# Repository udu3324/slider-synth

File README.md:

# Slider Synth

A synth that uses a linear touch sensor with a force sensor underneath to create cool sounds. It is inspired by the modulin by wintergatan. Powered by the esp32-s3 and mozzi library.

## Purpose

I built this pcb to make my diy setup more professional. I originally hooked everything up with an arduino but was really hard to cary around without dropping the breadboard or unplugging something. This design leaves it hot pluggable as well as super professional and more polished. 

## Schematic

## Additional Notes

[rotary encoder model](https://github.com/KiCad/kicad-packages3D/issues/547)

[sot-223 model](https://grabcad.com/library/discrete-smd-1/details?folder_id=1300113)

## BOM

I am supplying my own esp32-s3, rotary encoder, buttons, leds, and some other stuff that would cause the price to spike up to $30

I also have the linear softpot potentiometer, force sensitive resistor, and plywood strip on hand. **They total about $50** (plywood was scrap/free)

**Before fabricating the pcb, make sure the traces for the FSR is going to IO4 and not IO38!!!**

| Price  | Part Number            | Type     | LCSC Part   | Owner    | Designators          |   Qty | Manufacturer   |
|:-------|:-----------------------|:---------|:------------|:---------|:---------------------|------:|:---------------|
| $0.02  | CL21A106KAYNNNE        | Basic    | C15850      | System   | C4                   |     2 | JLCPCB         |
| $0.17  | CL21A476MQYNNNE        | Basic    | C16780      | System   | C3,C43,C45           |     6 | JLCPCB         |
| $0.03  | SS14                   | Basic    | C2480       | System   | D1                   |     2 | JLCPCB         |
| $0.02  | CL21B105KBFNNNE        | Basic    | C28323      | System   | C1                   |     2 | JLCPCB         |
| $2.11  | LM3940IMPX-3.3/NOPB    | Extended | C544820     | System   | U2                   |     2 | JLCPCB         |
| $0.05  | CC0805KRX7R9BB104      | Basic    | C49678      | System   | C48,C49,C5,C50,C6,C7 |    12 | JLCPCB         |
| $0.37  | LM386                  | Extended | C5157706    | System   | U33,U34              |     4 | JLCPCB         |
| $0.03  | CL21B474KBFNNNE        | Basic    | C13967      | System   | C2                   |     2 | JLCPCB         |
| $0.01  | 0805W8F0000T5E         | Basic    | C17477      | System   | R4,R5,R6             |     6 | JLCPCB         |
| $5.35  | MCP4922-E/SL           | Extended | C39851      | System   | U32                  |     2 | JLCPCB         |
| $0.01  | 0805W8F1002T5E         | Basic    | C17414      | System   | R13,R3               |     4 | JLCPCB         |
| $0.01  | 0805W8F100JT5E         | Basic    | C17415      | System   | R28,R29              |     4 | JLCPCB         |
| $2.24  | USB4105-GF-A-120       | Extended | C5184243    | System   | J1                   |     2 | JLCPCB         |
| $0.03  | 0805B333K500NT         | Basic    | C1739       | System   | C42,C44              |     4 | JLCPCB         |
| $0.01  | 0805W8F3300T5E         | Basic    | C17630      | System   | R10,R11,R8,R9        |     8 | JLCPCB         |
| $0.05  | CL21B473KBCNNNC        | Basic    | C53134      | Customer | C46,C47              |     4 | JLCPCB         |
| $0.01  | 0805W8F5101T5E         | Basic    | C27834      | System   | R1,R2                |     4 | JLCPCB         |
| $23.28 | **Total Part Price**   |          |             |          |                      |       |                |
|        |                        |          |             |          |                      |       |                |
| $37.24 | Merchandise Total      |          |             |          |                      |       |                |
| $26.56 | Shipping Estimate      |          |             |          |                      |       |                |
| $5.27  | Sales Tax              |          |             |          |                      |       |                |
| $20.49 | Customs duties & taxes |          |             |          |                      |       |                |
| $89.56 | **Grand Total**        |          |             |          |                      |       |                |

Actual total would be around ~$150 USD including my own components sourced.

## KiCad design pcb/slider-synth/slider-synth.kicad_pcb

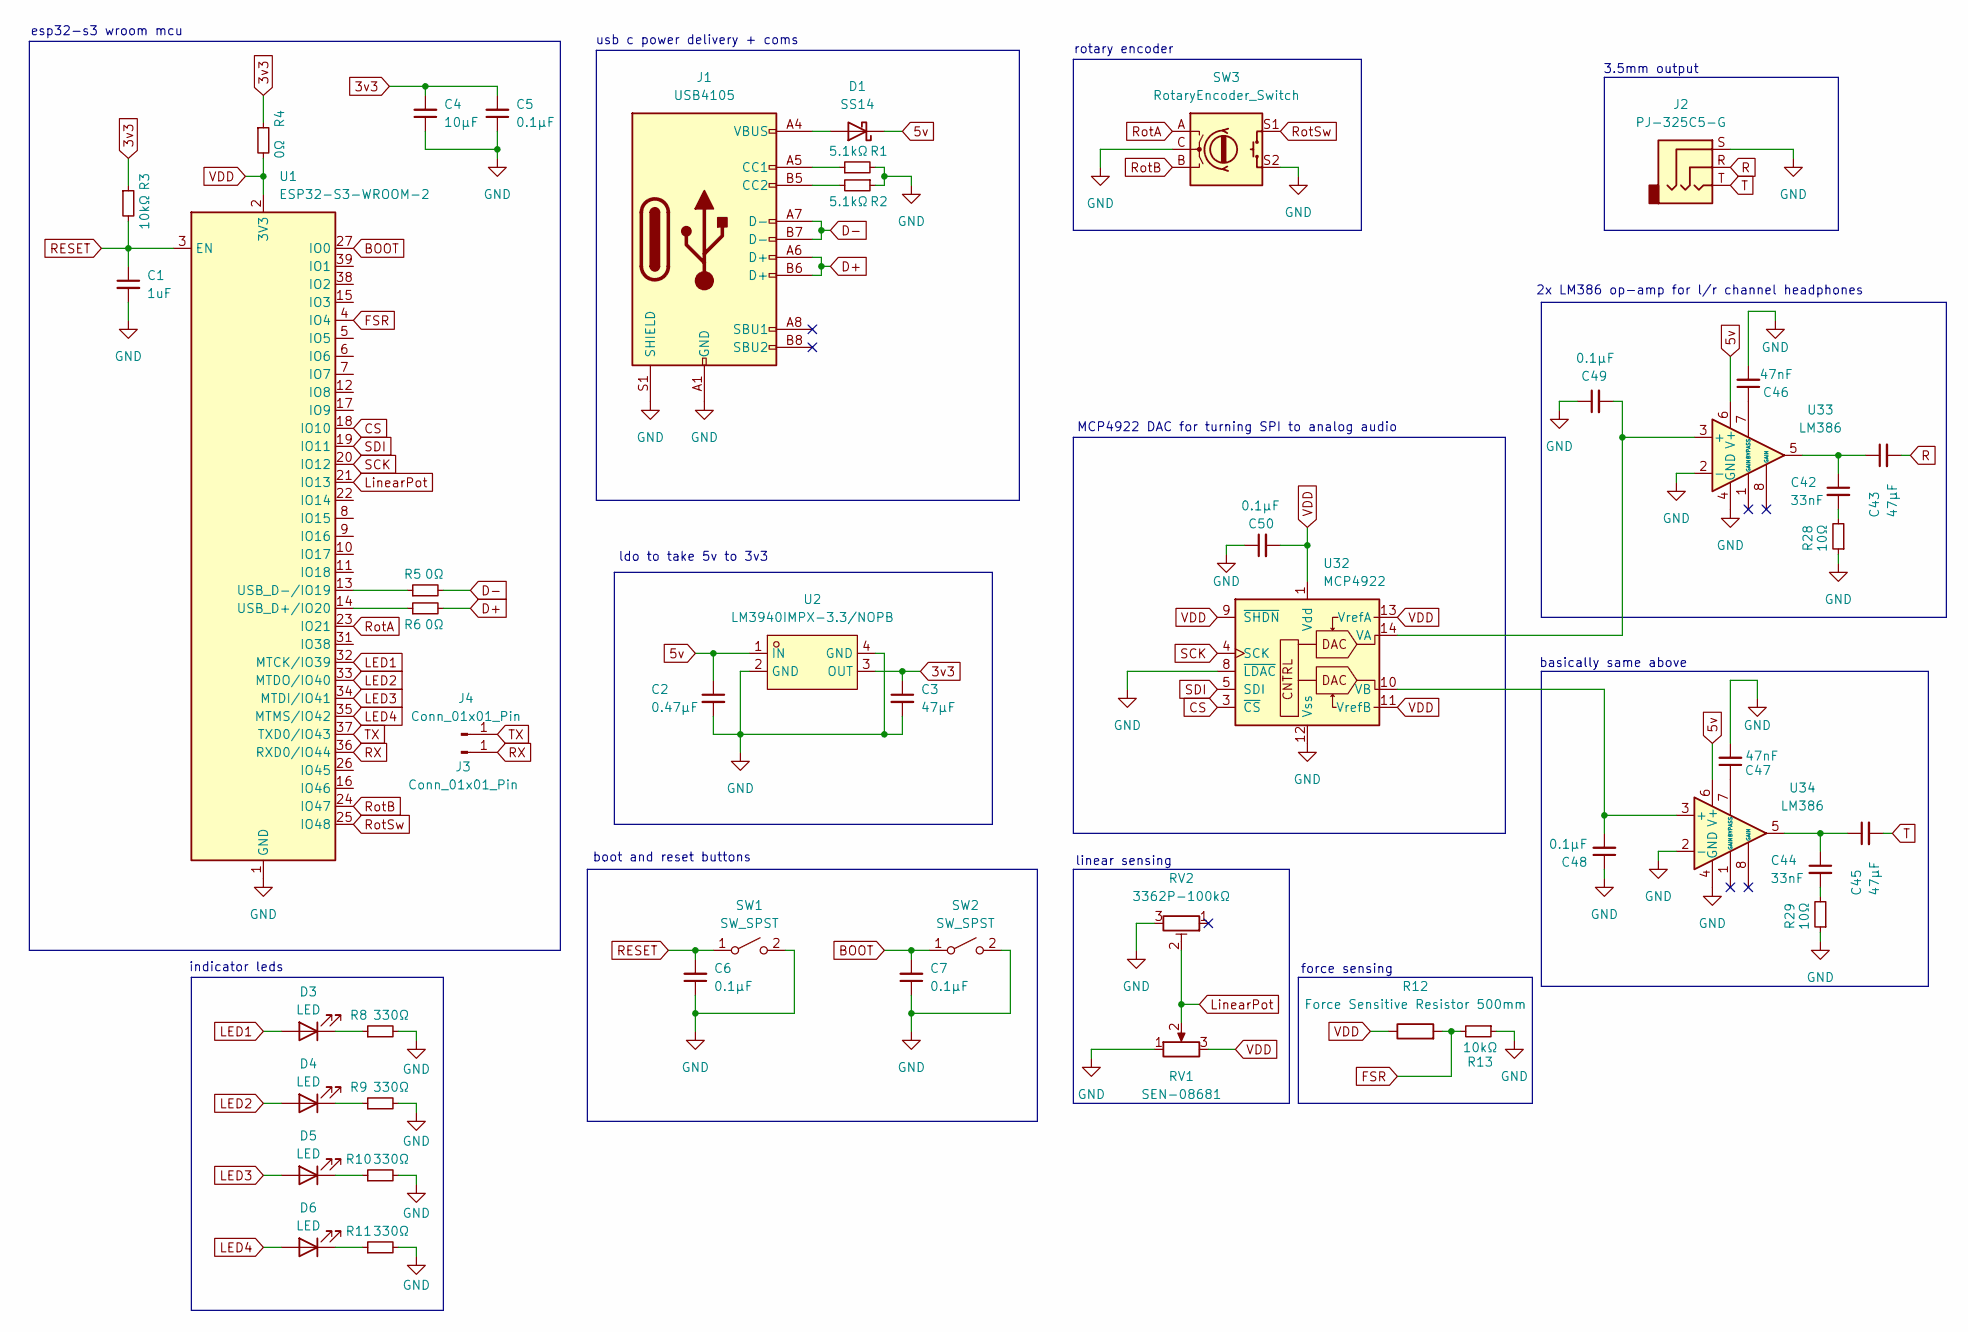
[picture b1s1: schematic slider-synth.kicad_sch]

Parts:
C1: 1uF; C_0805_2012Metric
C2: 0.47μF; C_0805_2012Metric
C3, C43, C45: 47μF; C_0805_2012Metric
C4: 10μF; C_0805_2012Metric
C5, C6, C7, C48, C49, C50: 0.1μF; C_0805_2012Metric
C42, C44: 33nF; C_0805_2012Metric
C46, C47: 47nF; C_0805_2012Metric
D1: SS14; D_SMA
D3, D4, D5, D6: LED; LED_D5.0mm
J1: USB4105; USB_C_Receptacle_GCT_USB4105-xx-A_16P_TopMnt_Horizontal
J2: PJ-325C5-G; Jack_3.5mm_CUI_SJ1-3535NG_Horizontal; LCSC C692438
J3, J4: Conn_01x01_Pin; PinHeader_1x01_P2.54mm_Vertical
R1, R2: 5.1kΩ; R_0805_2012Metric
R3, R13: 10kΩ; R_0805_2012Metric
R4, R5, R6: 0Ω; R_0805_2012Metric
R8, R9, R10, R11: 330Ω; R_0805_2012Metric
R12: Force Sensitive Resistor 500mm; PinSocket_1x02_P2.54mm_Vertical
R28, R29: 10Ω; R_0805_2012Metric
RV1: SEN-08681; PinSocket_1x03_P2.54mm_Vertical
RV2: 3362P-100kΩ; POT_3362P
SW1, SW2: SW_SPST; SW_PUSH_6mm
SW3: RotaryEncoder_Switch; RotaryEncoder_Alps_EC11E-Switch_Vertical_H20mm
U1: ESP32-S3-WROOM-2
U2: LM3940IMPX-3.3/NOPB; SOT-223-4_L6.5-W3.5-P2.30-LS7.0-BR; LCSC Part C544820
U32: MCP4922; SOIC-14_3.9x8.7mm_P1.27mm
U33, U34: LM386; SOIC-8_3.9x4.9mm_P1.27mm

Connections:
3v3: C3.1, C4.2, C5.2, R3.1, R4.1, U2.3 (OUT)
5v: C2.1, D1.1 (K), U2.1 (IN), U33.6 (V+), U34.6 (V+)
BOOT: C7.2, SW2.1 (A), U1.27 (IO0)
CS: U1.18 (IO10), U32.3 (~CS)
D+: J1.A6 (D+), J1.B6 (D+), R6.2
D-: J1.A7 (D-), J1.B7 (D-), R5.2
FSR: R12.2, R13.2, U1.4 (IO4)
GND: C1.2, C2.2, C3.2, C4.1, C5.1, C6.1, C7.1, C46.2, C47.2, C48.1, C49.1, C50.1, J1.A1 (GND), J1.A12 (GND), J1.B1 (GND), J1.B12 (GND), J1.S1 (SHIELD), J2.S, R1.2, R2.1, R8.2, R9.2, R10.2, R11.2, R13.1, R28.1, R29.1, RV1.1, RV2.3, SW1.2 (B), SW2.2 (B), SW3.C, SW3.S2, U1.1 (GND), U1.40 (GND), U1.41 (GND), U2.2 (GND), U2.4 (GND), U32.8 (~LDAC), U32.12 (Vss), U33.2 (-), U33.4 (GND), U34.2 (-), U34.4 (GND)
LED1: D3.2 (A), U1.32 (MTCK/IO39)
LED2: D4.2 (A), U1.33 (MTDO/IO40)
LED3: D5.2 (A), U1.34 (MTDI/IO41)
LED4: D6.2 (A), U1.35 (MTMS/IO42)
LinearPot: RV1.2, RV2.2, U1.21 (IO13)
unnamed: C42.1, C43.1, U33.5
unnamed: C42.2, R28.2
unnamed: C44.1, C45.1, U34.5
unnamed: C44.2, R29.2
unnamed: D1.2 (A), J1.A4 (VBUS), J1.A9 (VBUS), J1.B4 (VBUS), J1.B9 (VBUS)
unnamed: D3.1 (K), R8.1
unnamed: D4.1 (K), R9.1
unnamed: D5.1 (K), R10.1
unnamed: D6.1 (K), R11.1
unnamed: J1.A5 (CC1), R1.1
unnamed: J1.B5 (CC2), R2.2
unnamed: R6.1, U1.14 (USB_D+/IO20)
unnamed: R5.1, U1.13 (USB_D-/IO19)
unnamed: C49.2, U32.14 (VA), U33.3 (+)
unnamed: C48.2, U32.10 (VB), U34.3 (+)
unnamed: C46.1, U33.7 (BYPASS)
unnamed: C47.1, U34.7 (BYPASS)
R: C43.2, J2.R
RESET: C1.1, C6.2, R3.2, SW1.1 (A), U1.3 (EN)
RX: J3.1, U1.36 (RXD0/IO44)
RotA: SW3.A, U1.23 (IO21)
RotB: SW3.B, U1.24 (IO47)
RotSw: SW3.S1, U1.25 (IO48)
SCK: U1.20 (IO12), U32.4 (SCK)
SDI: U1.19 (IO11), U32.5 (SDI)
T: C45.2, J2.T
TX: J4.1, U1.37 (TXD0/IO43)
VDD: C50.2, R4.2, R12.1, RV1.3, U1.2 (3V3), U32.1 (Vdd), U32.9 (~SHDN), U32.11 (VrefB), U32.13 (VrefA)

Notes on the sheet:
esp32-s3 wroom mcu
MCP4922 DAC for turning SPI to analog audio
3.5mm output
force sensing
basically same above
rotary encoder
usb c power delivery + coms
ldo to take 5v to 3v3
2x LM386 op-amp for l/r channel headphones
boot and reset buttons
indicator leds
linear sensing

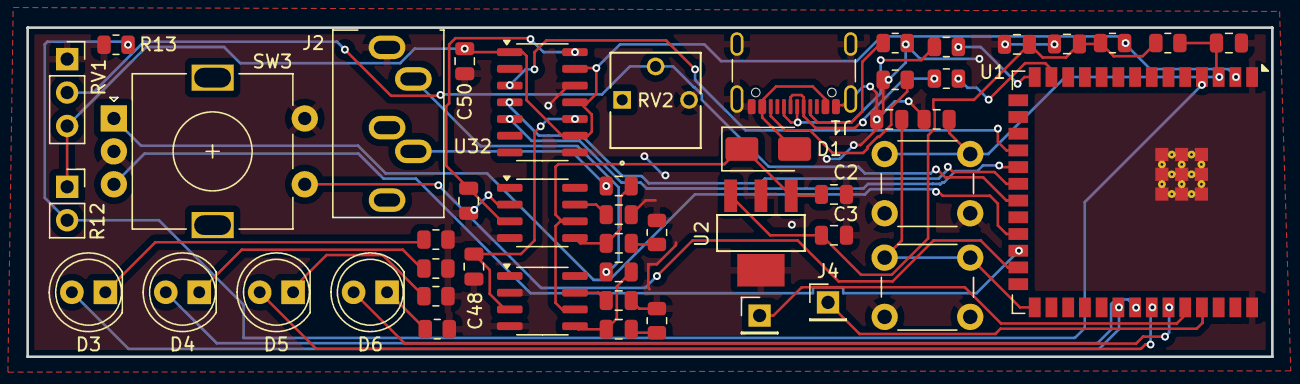
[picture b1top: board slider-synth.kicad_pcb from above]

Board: 2 copper layers, 94.6 x 25.0 mm, 49 parts (0 on the bottom side), 41 nets.

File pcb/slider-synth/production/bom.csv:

Designator,Footprint,Quantity,Value,LCSC Part #
C1,0805,1,1uF,
C2,0805,1,0.47μF,
"C3, C43, C45",0805,3,47μF,
C4,0805,1,10μF,
"C42, C44",0805,2,33nF,
"C46, C47",0805,2,0.05μF,
"C48, C49, C5, C50, C6, C7",0805,6,0.1μF,
D1,D_SMA,1,SS14,
"D3, D4, D5, D6",LED_D5.0mm,4,LED,
J1,USB_C_Receptacle_GCT_USB4105-xx-A_16P_TopMnt_Horizontal,1,USB4105,
J2,Jack_3.5mm_CUI_SJ1-3535NG_Horizontal,1,PJ-325C5-G,C692438
"J3, J4",PinHeader_1x01_P2.54mm_Vertical,2,Conn_01x01_Pin,
"R1, R2",0805,2,5.1kΩ,
"R10, R11, R8, R9",0805,4,330Ω,
R12,PinSocket_1x02_P2.54mm_Vertical,1,Force Sensitive Resistor 500mm,
"R13, R3",0805,2,10kΩ,
"R28, R29",0805,2,10Ω,
"R4, R5, R6",0805,3,0Ω,
RV1,PinSocket_1x03_P2.54mm_Vertical,1,SEN-08681,
RV2,POT_3362P,1,3362P-100kΩ,
"SW1, SW2",SW_PUSH_6mm,2,SW_SPST,
SW3,RotaryEncoder_Alps_EC11E-Switch_Vertical_H20mm,1,RotaryEncoder_Switch,
U1,ESP32-S3-WROOM-2,1,ESP32-S3-WROOM-2,
U2,SOT-223-4_L6.5-W3.5-P2.30-LS7.0-BR,1,LM3940IMPX-3.3/NOPB,C544820
U32,SOIC-14_3.9x8.7mm_P1.27mm,1,MCP4922,
"U33, U34",SOIC-8_3.9x4.9mm_P1.27mm,2,LM386,

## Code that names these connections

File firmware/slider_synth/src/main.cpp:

#include "MozziConfigValues.h"  // for named option values

#define MOZZI_AUDIO_MODE MOZZI_OUTPUT_EXTERNAL_TIMED
#define MOZZI_AUDIO_BITS 24
#define MOZZI_CONTROL_RATE 256 // Hz, powers of 2 are most reliable

#include <Mozzi.h>
#include <Oscil.h>
#include <tables/sin2048_int8.h> // table for Oscils to play

#include <SPI.h>
#include <DAC_MCP49xx.h>  // https://github.com/tomcombriat/DAC_MCP49XX 
// which is an adapted fork from https://github.com/exscape/electronics/tree/master/Arduino/Libraries/DAC_MCP49xx  (Thomas Backman)
#include <ESP32Encoder.h>
#include <Ticker.h>

#define Linear_Pot_Pin 13 // Linear Potentiometer
#define FSR_Pin 4 // Force Sensitive Resistor

#define LED0_Pin 39
#define LED1_Pin 40
#define LED2_Pin 41
#define LED3_Pin 42

#define TX_Pin 43
#define RX_Pin 44

#define Rotary_A_Pin 21
#define Rotary_B_Pin 47
#define Rotary_Button_Pin 48

#define SPI_SCK   12  // SCK (Clock)
#define SPI_MOSI  11  // SDI (MOSI)
#define SPI_MISO  9   // SDO (MISO) UNUSED, NOT ON THE MCP4922
// External audio output parameters and DAC declaration
#define SS_PIN 10  // if you are on AVR and using PortWrite you need still need to put the pin you are actually using: 7 on Uno, 38 on Mega
#define BITS_PER_CHANNEL 12  // each channel of the DAC is outputting 12 bits

const int fsr_vel_start = 18000;
const int fsr_velocity_limit = 56688;

int starting_octave = 3; //cant be less than 0
const int scale = 3; //scale of octaves playable

int pitch; //27.5hz-4186hz
int velocity; //0-127

const float base_freq = 32.703; // C1
float hz_map_low;
float hz_map_high;

float depth = 0.02;

//not me
const float depth_min = 0.0;
const float depth_max = 0.2;
const float depth_step = 0.01;

float vibrato_speed = 6.5;
const float vibrato_speed_min = 1.0;
const float vibrato_speed_max = 15.0;
const float vibrato_speed_step = 0.5;

float filter_cutoff = 1.0;
const float filter_cutoff_min = 0.1;
const float filter_cutoff_max = 2.0;
const float filter_cutoff_step = 0.1;
//not me above

int mode = 0;
int changing_to = 0;
bool changing_mode = false;

// Synthesis part
Oscil <SIN2048_NUM_CELLS, MOZZI_AUDIO_RATE> aSin(SIN2048_DATA);
Oscil <2048, MOZZI_CONTROL_RATE> kVib(SIN2048_DATA);

DAC_MCP49xx dac(DAC_MCP49xx::MCP4922, SS_PIN);

ESP32Encoder encoder;

int linear_val;
int force_val;
int encoder_count = 0;
bool slow_down = false;

void ledModeFlash();

Ticker ledModeFlashTimer(ledModeFlash, 100);

void ledModeFlash() {

  digitalWrite(LED0_Pin, LOW);
  digitalWrite(LED1_Pin, LOW);
  digitalWrite(LED2_Pin, LOW);
  digitalWrite(LED3_Pin, LOW);

  if (changing_mode) {
    switch (changing_to) {
      case 0:
        digitalWrite(LED0_Pin, !digitalRead(LED0_Pin));
        break;
      case 1:
        digitalWrite(LED1_Pin, !digitalRead(LED1_Pin));
        break;
      case 2:
        digitalWrite(LED2_Pin, !digitalRead(LED2_Pin));
        break;
      case 3:
        digitalWrite(LED3_Pin, !digitalRead(LED3_Pin));
        break;
    }
  } else {
    switch (mode) {
      case 0:
        digitalWrite(LED0_Pin, HIGH);
        break;
      case 1:
        digitalWrite(LED1_Pin, HIGH);
        break;
      case 2:
        digitalWrite(LED2_Pin, HIGH);
        break;
      case 3:
        digitalWrite(LED3_Pin, HIGH);
        break;
    }
  }
}

void buttonSlowDown();

Ticker slowDownTimer(buttonSlowDown, 1000);

void buttonSlowDown() {
  slow_down = false;
}

void generateHz() {
  hz_map_low = base_freq * pow(2, starting_octave - 1);
  hz_map_high = hz_map_low * pow(2, scale);
}

void octaveUp() {
  if (starting_octave >= 8) return;

  starting_octave++;
  generateHz();
}

void octaveDown() {
  if (starting_octave <= -2) return;

  starting_octave--;
  generateHz();
}

void vibratoUp() {
  if (depth >= depth_max) return;
  
  depth += depth_step;
  if (depth > depth_max) depth = depth_max;
}

void vibratoDown() {
  if (depth <= depth_min) return;
  
  depth -= depth_step;
  if (depth < depth_min) depth = depth_min;
}

void vibratoSpeedUp() {
  if (vibrato_speed >= vibrato_speed_max) return;
  
  vibrato_speed += vibrato_speed_step;
  if (vibrato_speed > vibrato_speed_max) vibrato_speed = vibrato_speed_max;
  
  kVib.setFreq(vibrato_speed);
}

void vibratoSpeedDown() {
  if (vibrato_speed <= vibrato_speed_min) return;
  
  vibrato_speed -= vibrato_speed_step;
  if (vibrato_speed < vibrato_speed_min) vibrato_speed = vibrato_speed_min;
  
  kVib.setFreq(vibrato_speed);
}

void filterUp() {
  if (filter_cutoff >= filter_cutoff_max) return;
  
  filter_cutoff += filter_cutoff_step;
  if (filter_cutoff > filter_cutoff_max) filter_cutoff = filter_cutoff_max;
}

void filterDown() {
  if (filter_cutoff <= filter_cutoff_min) return;
  
  filter_cutoff -= filter_cutoff_step;
  if (filter_cutoff < filter_cutoff_min) filter_cutoff = filter_cutoff_min;
}

void runEncoderModeUp() {
  switch (mode) {
    case 0:
      octaveUp();
      break;
    case 1:
      vibratoUp();
      break;
    case 2:
      vibratoSpeedUp();
      break;
    case 3:
      filterUp();
      break;
  }
}

void runEncoderModeDown() {
  switch (mode) {
    case 0:
      octaveDown();
      break;
    case 1:
      vibratoDown();
      break;
    case 2:
      vibratoSpeedDown();
      break;
    case 3:
      filterDown();
      break;
  }
}

void audioOutput(const AudioOutput f) // f is a structure containing both channels
{

  int out = MOZZI_AUDIO_BIAS + f.l();

  unsigned short lowBits = (unsigned short) out;  //
  unsigned short highBits =  out >> BITS_PER_CHANNEL;

  dac.output2(highBits, lowBits);  // outputs the two channels in one call.
}

void setup() {
  // serial for uart
  Serial.begin(115200, SERIAL_8N1, RX, TX);

  Serial.println("udu3324 was here!!");

  // Set custom SPI pins
  SPI.begin(SPI_SCK, SPI_MISO, SPI_MOSI);

  dac.init();   // start SPI communications
  //dac.setPortWrite(true);  //comment this line if you do not want to use PortWrite (for non-AVR platforms)
  
  //calculate the starting hz
  generateHz();

  //vibrato setup
  kVib.setFreq(vibrato_speed);

  pinMode(LED0_Pin, OUTPUT);
  pinMode(LED1_Pin, OUTPUT);
  pinMode(LED2_Pin, OUTPUT);
  pinMode(LED3_Pin, OUTPUT);

  pinMode(Rotary_A_Pin, INPUT_PULLUP);
  pinMode(Rotary_B_Pin, INPUT_PULLUP);

  pinMode(Rotary_Button_Pin, INPUT_PULLUP);

  encoder.attachSingleEdge(Rotary_A_Pin, Rotary_B_Pin);
  encoder.setCount(0);

  startMozzi();
  Serial.println("on!!!!!!!!");

  ledModeFlashTimer.start();
  slowDownTimer.start();

}

// Carry enveloppes
float filter_memory = 0.0; // For simple low-pass filter

void updateControl() {
  Serial.println("it is looping!!!");

  if (digitalRead(Rotary_Button_Pin) == LOW && !slow_down) {
    changing_mode = !changing_mode;

    if (!changing_mode) {
      mode = changing_to;
    }

    slow_down = true;
  }

  if (encoder.getCount() > encoder_count) {
    if (changing_mode && changing_to < 3 ) {
      changing_to = changing_to + 1;
    } else {
      runEncoderModeUp();
    }
  } else if (encoder.getCount() < encoder_count) {
    if (changing_mode && changing_to > 0 ) {
      changing_to = changing_to - 1;
    } else {
      runEncoderModeDown();
    }
  }

  encoder_count = encoder.getCount();

  ledModeFlashTimer.update();
  slowDownTimer.update();

  linear_val = mozziAnalogRead16(Linear_Pot_Pin);
  force_val = mozziAnalogRead16(FSR_Pin);

  //map to freq and vel
  pitch = map(linear_val, 0, 65536, hz_map_low, hz_map_high);
  velocity = map(force_val, fsr_vel_start, fsr_velocity_limit, 0, 20);

  //hard limits
  if ((linear_val == 0)) pitch = 0; //stop mapping of zero
  if (velocity > 127) velocity = 127; //stop higher mappings

  //stop negative numbers for some reason
  if (velocity < 0) velocity = 0;

  float vibrato = (velocity * depth) * kVib.next();

  Serial.print("p = \t");
  Serial.print(pitch);
  Serial.print("\t v = ");
  Serial.println(velocity);

  if (linear_val > 0) {
    aSin.setFreq(pitch + vibrato);
  } else {
    aSin.setFreq(0);
  }
}

AudioOutput updateAudio() {
  int32_t sample = (int32_t)aSin.next();
  
  // Apply simple low-pass filter (cutoff controlled by filter_cutoff)
  float alpha = filter_cutoff / (filter_cutoff + 1.0);
  filter_memory = alpha * sample + (1.0 - alpha) * filter_memory;
  
  int32_t filtered_sample = (int32_t)filter_memory;
  
  return MonoOutput::fromNBit(24, filtered_sample); // specify that the audio we are sending here is 24 bits.
}

void loop() {  
  audioHook();
}

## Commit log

2025-07-24 add pcb
2025-07-25 update schem
2025-07-25 price optimizations
2025-07-25 add fsr and linear pot
2025-07-25 footprints and routing
2025-07-25 prod files, cad, and cool silkscreen
2025-07-25 Add bom, readme/journal stuff
2025-08-05 firmware wip
2025-08-06 fixed audio out
2025-08-06 add vibrato
2025-08-07 add modes
2025-08-07 move io38 to io4, but did not update prod files
2026-03-29 blog post md
2026-03-29 better formatting
